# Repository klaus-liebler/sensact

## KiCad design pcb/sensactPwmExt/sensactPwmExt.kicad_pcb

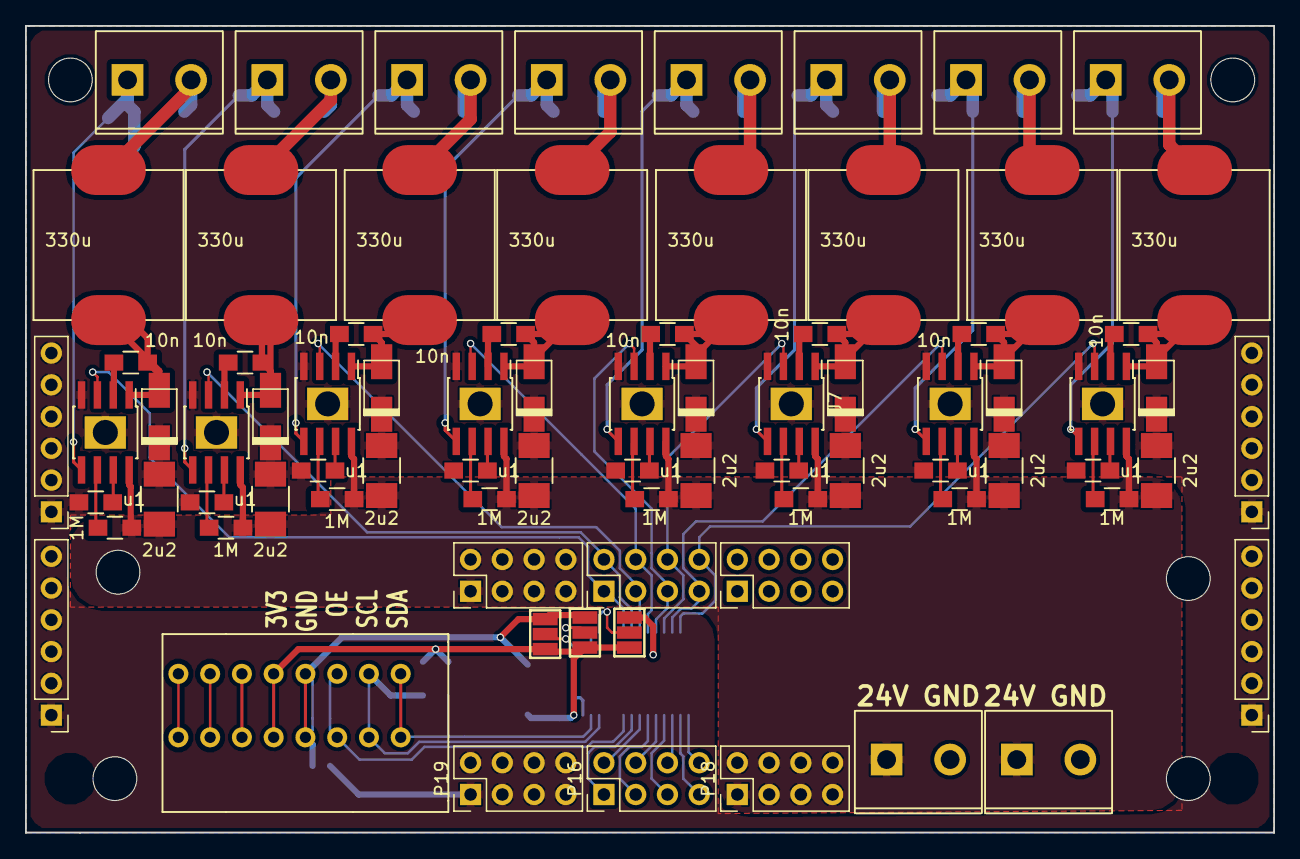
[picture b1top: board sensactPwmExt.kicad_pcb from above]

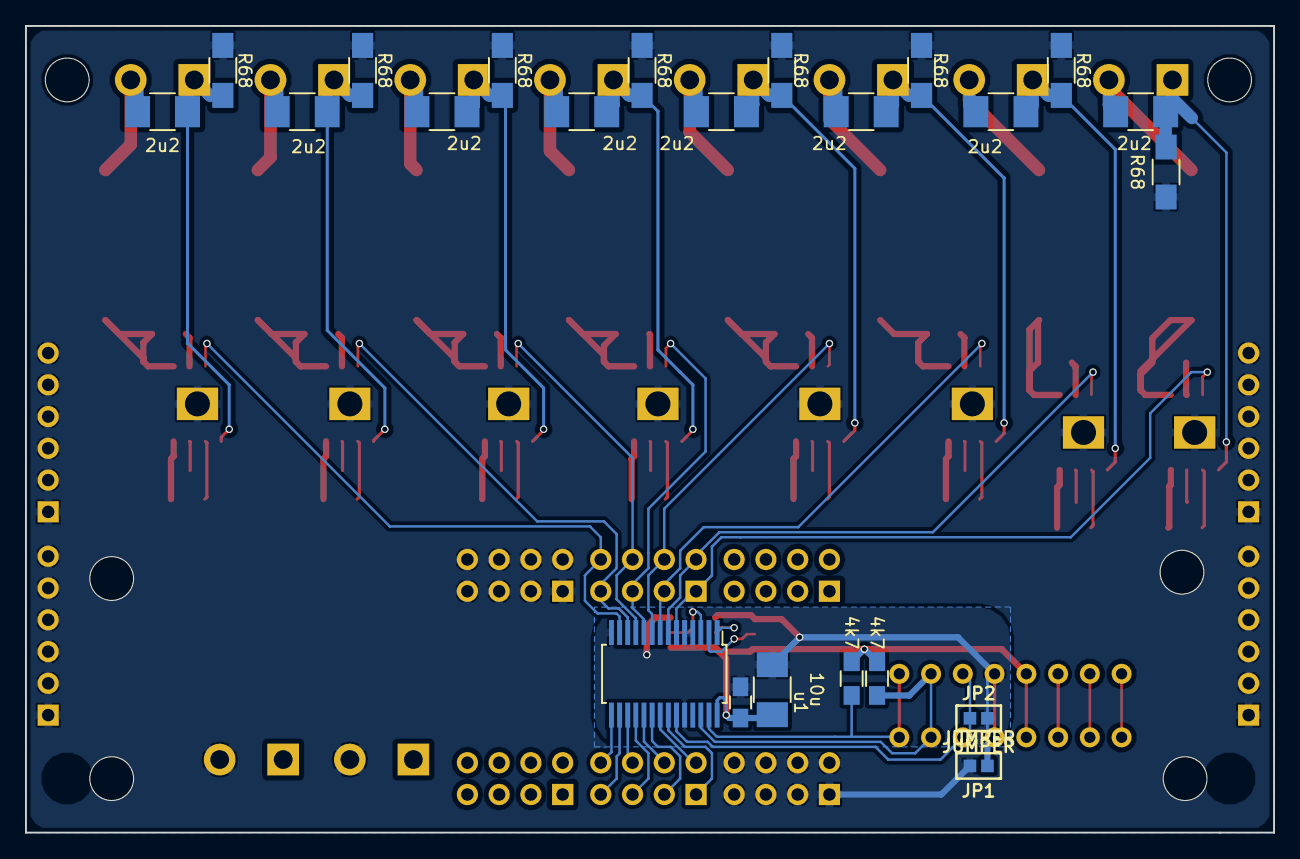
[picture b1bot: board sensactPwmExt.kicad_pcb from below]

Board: 2 copper layers, 99.8 x 64.5 mm, 109 parts (23 on the bottom side), 74 nets.

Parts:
C8: u1; C_0805_HandSoldering
C9: 10u; C_1210_HandSoldering
C10, C13, C14, C17, C18, C21, C22, C25, C26, C29, C30, C33, C34, C37, C38, C41: 2u2; R_1210_HandSoldering
C11, C15, C19, C23, C27, C31, C35, C39: 10n; R_0805_HandSoldering
C12, C16, C20, C24, C28, C32, C36, C40: u1; R_0805_HandSoldering
D1, D2, D3, D4, D5, D6, D7, D8: D_Schottky; do214ac_handsolder
JP1, JP2: JUMPER; SMD-solder-bridge
JP3, JP4, JP5: JUMPER3; SMD-solder-bridge-3pin
L1, L2, L3, L4, L5, L6, L7, L8: 330u; CD127
P1: CONN_01X08; KF141R-8p
P2, P2#2, P7, P8, P9, P10, P11, P12, P13, P14: CONN_01X02; conn_2P
P3, P4, P4#2, P5, P6, P6#2: CONN_01X01; MountingHole_3.5mm
P15, P16, P17, P18, P19, P20: CONN_01X08; Pin_Header_Straight_2x04_Pitch2.54mm
P21, P22, P23, P24: CONN_01X06; Pin_Header_Straight_1x06_Pitch2.54mm
R1, R2: 4k7; R_0805_HandSoldering
R3, R5, R7, R9, R11, R13, R15, R17: 1M; R_0805_HandSoldering
R4, R6, R8, R10, R12, R14, R16, R18: R68; R_1206_HandSoldering
U1: PCA9685; TSSOP-28_4.4x9.7mm_Pitch0.65mm_handsolder
U2, U3, U4, U5, U6, U7, U8, U9: LM3404; SOIC-8_3.9x4.9mm_Pitch1.27mm_pad_handsolder

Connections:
+3V3: C8.1, C9.1, JP3.1, JP4.1, JP5.1, P1.4, R1.1, R2.1, U1.28
+24V: C10.1, C14.1, C18.1, C22.1, C26.1, C30.1, C34.1, C38.1, P2.1, P2#2.1, P17.1, P17.2, P17.3, P17.4, P17.5, P17.6, P17.7, P17.8, P18.1, P18.2, P18.3, P18.4, P18.5, P18.6, P18.7, P18.8, R3.1, R5.1, R7.1, R9.1, R11.1, R13.1, R15.1, R17.1, U2.8, U3.8, U4.8, U5.8, U6.8, U7.8, U8.8, U9.8
/OE: JP2.1, P1.6, U1.23
/SCL: P1.7, R2.2, U1.26
/SDA: P1.8, R1.2, U1.27
/pwm1/LED+: C13.1, L1.1, P7.2
/pwm1/LED-: C13.2, P7.1, R4.1, U2.5
/pwm1/PWM_IN: P15.1, U1.6, U2.3
/pwm2/LED+: C17.1, L2.1, P8.2
/pwm2/LED-: C17.2, P8.1, R6.1, U3.5
/pwm2/PWM_IN: P15.2, U1.7, U3.3
/pwm3/LED+: C21.1, L3.1, P9.2
/pwm3/LED-: C21.2, P9.1, R8.1, U4.5
/pwm3/PWM_IN: P15.3, U1.8, U4.3
/pwm4/LED+: C25.1, L4.1, P10.2
/pwm4/LED-: C25.2, P10.1, R10.1, U5.5
/pwm4/PWM_IN: P15.4, U1.9, U5.3
/pwm5/LED+: C29.1, L5.1, P11.2
/pwm5/LED-: C29.2, P11.1, R12.1, U6.5
/pwm5/PWM_IN: P15.5, U1.10, U6.3
/pwm6/LED+: C33.1, L6.1, P12.2
/pwm6/LED-: C33.2, P12.1, R14.1, U7.5
/pwm6/PWM_IN: P15.6, U1.11, U7.3
/pwm7/LED+: C37.1, L7.1, P13.2
/pwm7/LED-: C37.2, P13.1, R16.1, U8.5
/pwm7/PWM_IN: P15.7, U1.12, U8.3
/pwm8/LED+: C41.1, L8.1, P14.2
/pwm8/LED-: C41.2, P14.1, R18.1, U9.5
/pwm8/PWM_IN: P15.8, U1.13, U9.3
GND: C10.2, C12.2, C14.2, C16.2, C18.2, C20.2, C22.2, C24.2, C26.2, C28.2, C30.2, C32.2, C34.2, C36.2, C38.2, C40.2, D1.2, D2.2, D3.2, D4.2, D5.2, D6.2, D7.2, D8.2, JP1.2, P2.2, P2#2.2, P19.1, P19.2, P19.3, P19.4, P19.5, P19.6, P19.7, P19.8, P20.1, P20.2, P20.3, P20.4, P20.5, P20.6, P20.7, P20.8, P21.1, P21.2, P21.3, P21.4, P21.5, P21.6, P22.1, P22.2, P22.3, P22.4, P22.5, P22.6, P23.1, P23.2, P23.3, P23.4, P23.5, P23.6, P24.1, P24.2, P24.3, P24.4, P24.5, P24.6, R4.2, R6.2, R8.2, R10.2, R12.2, R14.2, R16.2, R18.2, U2.4, U2.9, U3.4, U3.9, U4.4, U4.9, U5.4, U5.9, U6.4, U6.9, U7.4, U7.9, U8.4, U8.9, U9.4, U9.9
GNDA: C8.2, C9.2, JP1.1, JP2.2, JP3.3, JP4.3, JP5.3, P1.5, U1.4, U1.5, U1.14, U1.24
unnamed: C11.1, D1.1, L1.2, U2.1
unnamed: C11.2, U2.2
unnamed: C12.1, U2.7
unnamed: C15.1, D2.1, L2.2, U3.1
unnamed: C15.2, U3.2
unnamed: C16.1, U3.7
unnamed: C19.1, D3.1, L3.2, U4.1
unnamed: C19.2, U4.2
unnamed: C20.1, U4.7
unnamed: C23.1, D4.1, L4.2, U5.1
unnamed: C23.2, U5.2
unnamed: C24.1, U5.7
unnamed: C27.1, D5.1, L5.2, U6.1
unnamed: C27.2, U6.2
unnamed: C28.1, U6.7
unnamed: C31.1, D6.1, L6.2, U7.1
unnamed: C31.2, U7.2
unnamed: C32.1, U7.7
unnamed: C35.1, D7.1, L7.2, U8.1
unnamed: C35.2, U8.2
unnamed: C36.1, U8.7
unnamed: C39.1, D8.1, L8.2, U9.1
unnamed: C39.2, U9.2
unnamed: C40.1, U9.7
unnamed: JP3.2, U1.1
unnamed: JP4.2, U1.2
unnamed: JP5.2, U1.3
unnamed: P16.1, U1.22
unnamed: P16.2, U1.21
unnamed: P16.3, U1.20
unnamed: P16.4, U1.19
unnamed: P16.5, U1.18
unnamed: P16.6, U1.17
unnamed: P16.7, U1.16
unnamed: P16.8, U1.15
unnamed: R3.2, U2.6
unnamed: R5.2, U3.6
unnamed: R7.2, U4.6
unnamed: R9.2, U5.6
unnamed: R11.2, U6.6
unnamed: R13.2, U7.6
unnamed: R15.2, U8.6
unnamed: R17.2, U9.6

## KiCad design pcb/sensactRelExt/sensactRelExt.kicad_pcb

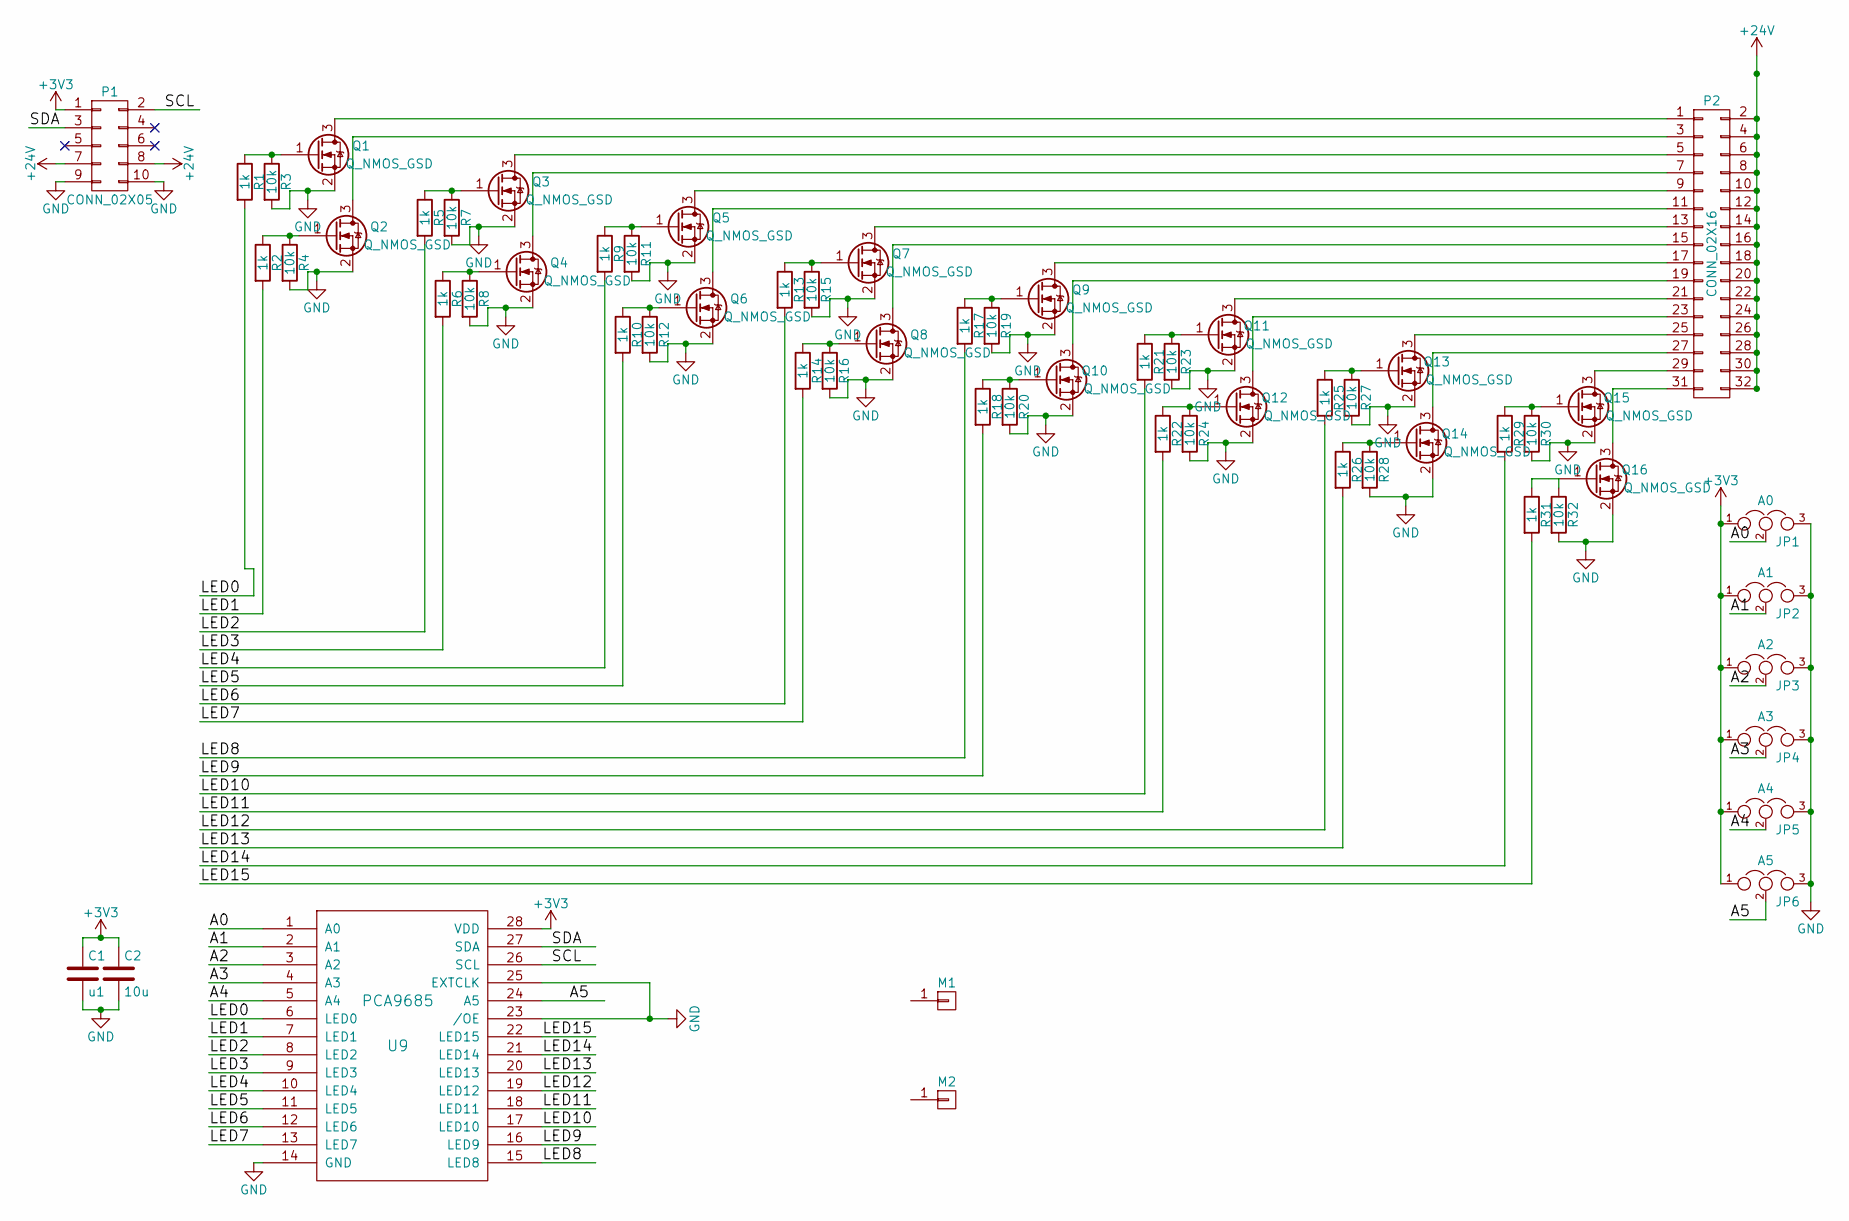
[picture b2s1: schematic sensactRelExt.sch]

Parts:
C1: u1; C_0805_HandSoldering
C2: 10u; C_1206_HandSoldering
JP1: A0; SMD-solder-bridge-3pin
JP2: A1; SMD-solder-bridge-3pin
JP3: A2; SMD-solder-bridge-3pin
JP4: A3; SMD-solder-bridge-3pin
JP5: A4; SMD-solder-bridge-3pin
JP6: A5; SMD-solder-bridge-3pin
M1, M2: CONN_01X01; MountingHole_4.3mm_M4_DIN965
P1: CONN_02X05; vasch_strip_5x2
P2: CONN_02X16; vasch_strip_16x2
Q1, Q2, Q3, Q4, Q5, Q6, Q7, Q8, Q9, Q10, Q11, Q12, Q13, Q14, Q15, Q16: Q_NMOS_GSD; SOT-23_Handsoldering
R1, R2, R5, R6, R9, R10, R13, R14, R17, R18, R21, R22, R25, R26, R29, R31: 1k; R_0805_HandSoldering
R3, R4, R7, R8, R11, R12, R15, R16, R19, R20, R23, R24, R27, R28, R30, R32: 10k; R_0805_HandSoldering
U9: PCA9685; TSSOP-28_4.4x9.7mm_Pitch0.65mm_handsolder

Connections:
+3V3: C1.1, C2.1, JP1.1, JP2.1, JP3.1, JP4.1, JP5.1, JP6.1, P1.1, U9.28 (VDD)
+24V: P1.7, P1.8, P2.2, P2.4, P2.6, P2.8, P2.10, P2.12, P2.14, P2.16, P2.18, P2.20, P2.22, P2.24, P2.26, P2.28, P2.30, P2.32
/A0: JP1.2, U9.1 (A0)
/A1: JP2.2, U9.2 (A1)
/A2: JP3.2, U9.3 (A2)
/A3: JP4.2, U9.4 (A3)
/A4: JP5.2, U9.5 (A4)
/A5: JP6.2, U9.24 (A5)
/LED0: R1.2, U9.6 (LED0)
/LED1: R2.2, U9.7 (LED1)
/LED2: R5.2, U9.8 (LED2)
/LED3: R6.2, U9.9 (LED3)
/LED4: R9.2, U9.10 (LED4)
/LED5: R10.2, U9.11 (LED5)
/LED6: R13.2, U9.12 (LED6)
/LED7: R14.2, U9.13 (LED7)
/LED8: R17.2, U9.15 (LED8)
/LED9: R18.2, U9.16 (LED9)
/LED10: R21.2, U9.17 (LED10)
/LED11: R22.2, U9.18 (LED11)
/LED12: R25.2, U9.19 (LED12)
/LED13: R26.2, U9.20 (LED13)
/LED14: R29.2, U9.21 (LED14)
/LED15: R31.2, U9.22 (LED15)
/SCL: P1.2, U9.26 (SCL)
/SDA: P1.3, U9.27 (SDA)
GND: C1.2, C2.2, JP1.3, JP2.3, JP3.3, JP4.3, JP5.3, JP6.3, P1.9, P1.10, Q1.2 (S), Q2.2 (S), Q3.2 (S), Q4.2 (S), Q5.2 (S), Q6.2 (S), Q7.2 (S), Q8.2 (S), Q9.2 (S), Q10.2 (S), Q11.2 (S), Q12.2 (S), Q13.2 (S), Q14.2 (S), Q15.2 (S), Q16.2 (S), R3.2, R4.2, R7.2, R8.2, R11.2, R12.2, R15.2, R16.2, R19.2, R20.2, R23.2, R24.2, R27.2, R28.2, R30.2, R32.2, U9.14 (GND), U9.23 (/OE), U9.25 (EXTCLK)
unnamed: P2.1, Q1.3 (D)
unnamed: P2.3, Q2.3 (D)
unnamed: P2.5, Q3.3 (D)
unnamed: P2.7, Q4.3 (D)
unnamed: P2.9, Q5.3 (D)
unnamed: P2.11, Q6.3 (D)
unnamed: P2.13, Q7.3 (D)
unnamed: P2.15, Q8.3 (D)
unnamed: P2.17, Q9.3 (D)
unnamed: P2.19, Q10.3 (D)
unnamed: P2.21, Q11.3 (D)
unnamed: P2.23, Q12.3 (D)
unnamed: P2.25, Q13.3 (D)
unnamed: P2.27, Q14.3 (D)
unnamed: P2.29, Q15.3 (D)
unnamed: P2.31, Q16.3 (D)
unnamed: Q1.1 (G), R1.1, R3.1
unnamed: Q2.1 (G), R2.1, R4.1
unnamed: Q3.1 (G), R5.1, R7.1
unnamed: Q4.1 (G), R6.1, R8.1
unnamed: Q5.1 (G), R9.1, R11.1
unnamed: Q6.1 (G), R10.1, R12.1
unnamed: Q7.1 (G), R13.1, R15.1
unnamed: Q8.1 (G), R14.1, R16.1
unnamed: Q9.1 (G), R17.1, R19.1
unnamed: Q10.1 (G), R18.1, R20.1
unnamed: Q11.1 (G), R21.1, R23.1
unnamed: Q12.1 (G), R22.1, R24.1
unnamed: Q13.1 (G), R25.1, R27.1
unnamed: Q14.1 (G), R26.1, R28.1
unnamed: Q15.1 (G), R29.1, R30.1
unnamed: Q16.1 (G), R31.1, R32.1

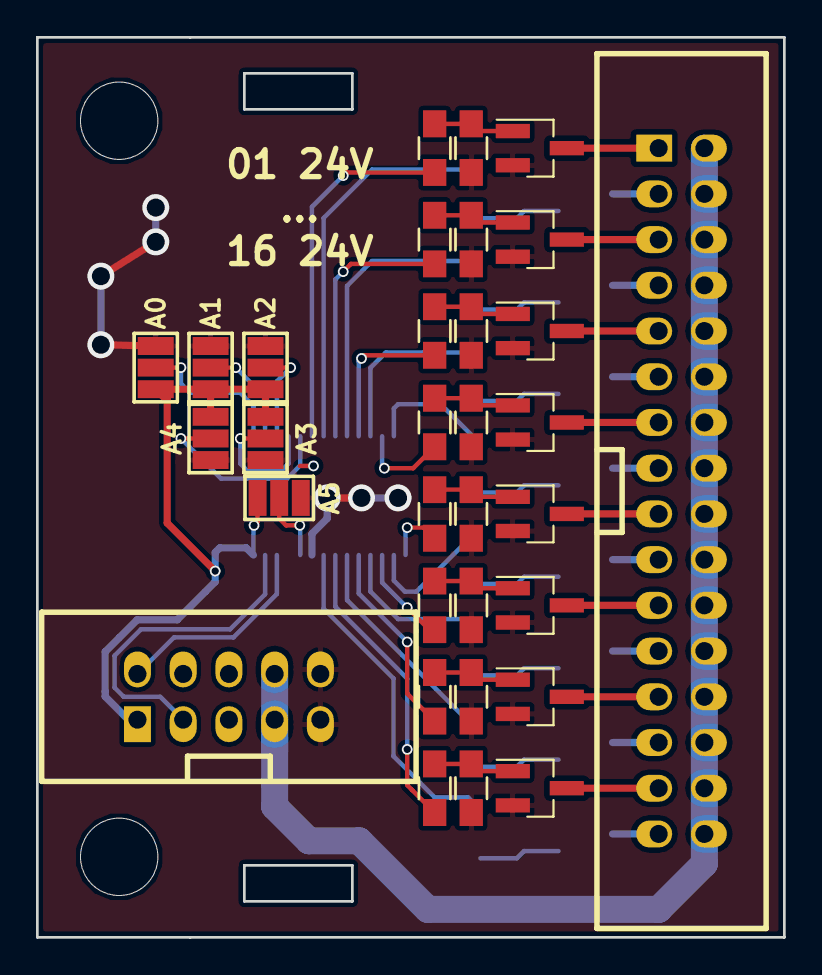
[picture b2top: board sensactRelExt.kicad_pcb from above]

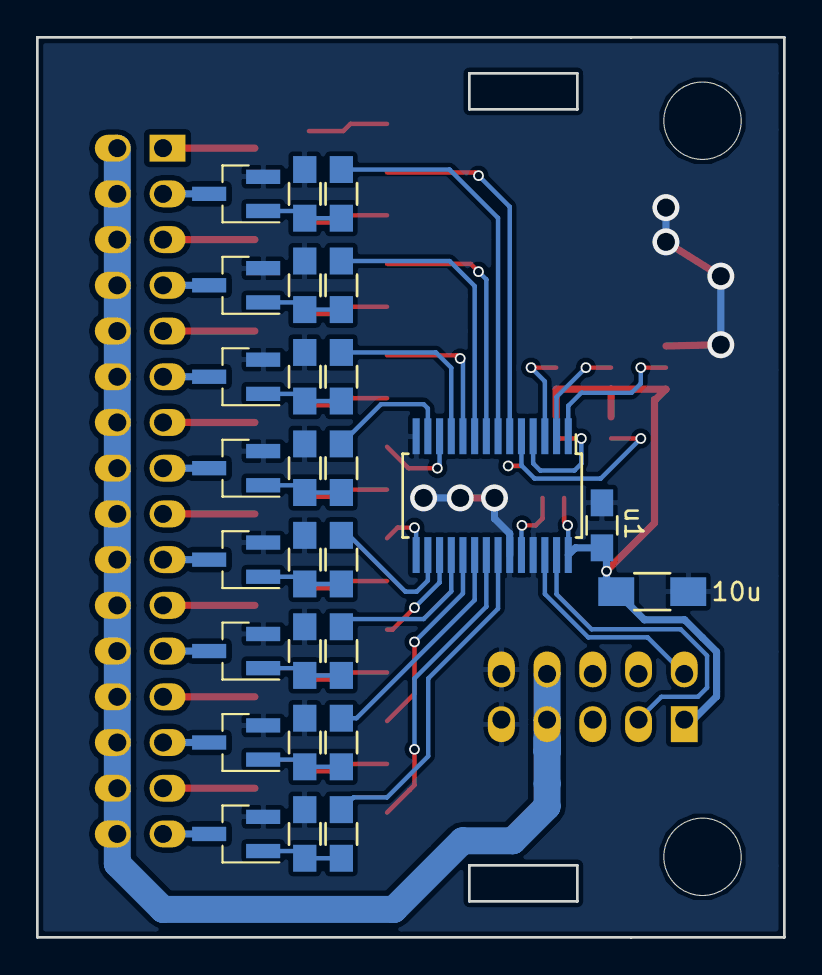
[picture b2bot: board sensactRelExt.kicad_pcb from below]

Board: 2 copper layers, 41.5 x 50.0 mm, 61 parts (27 on the bottom side), 59 nets.

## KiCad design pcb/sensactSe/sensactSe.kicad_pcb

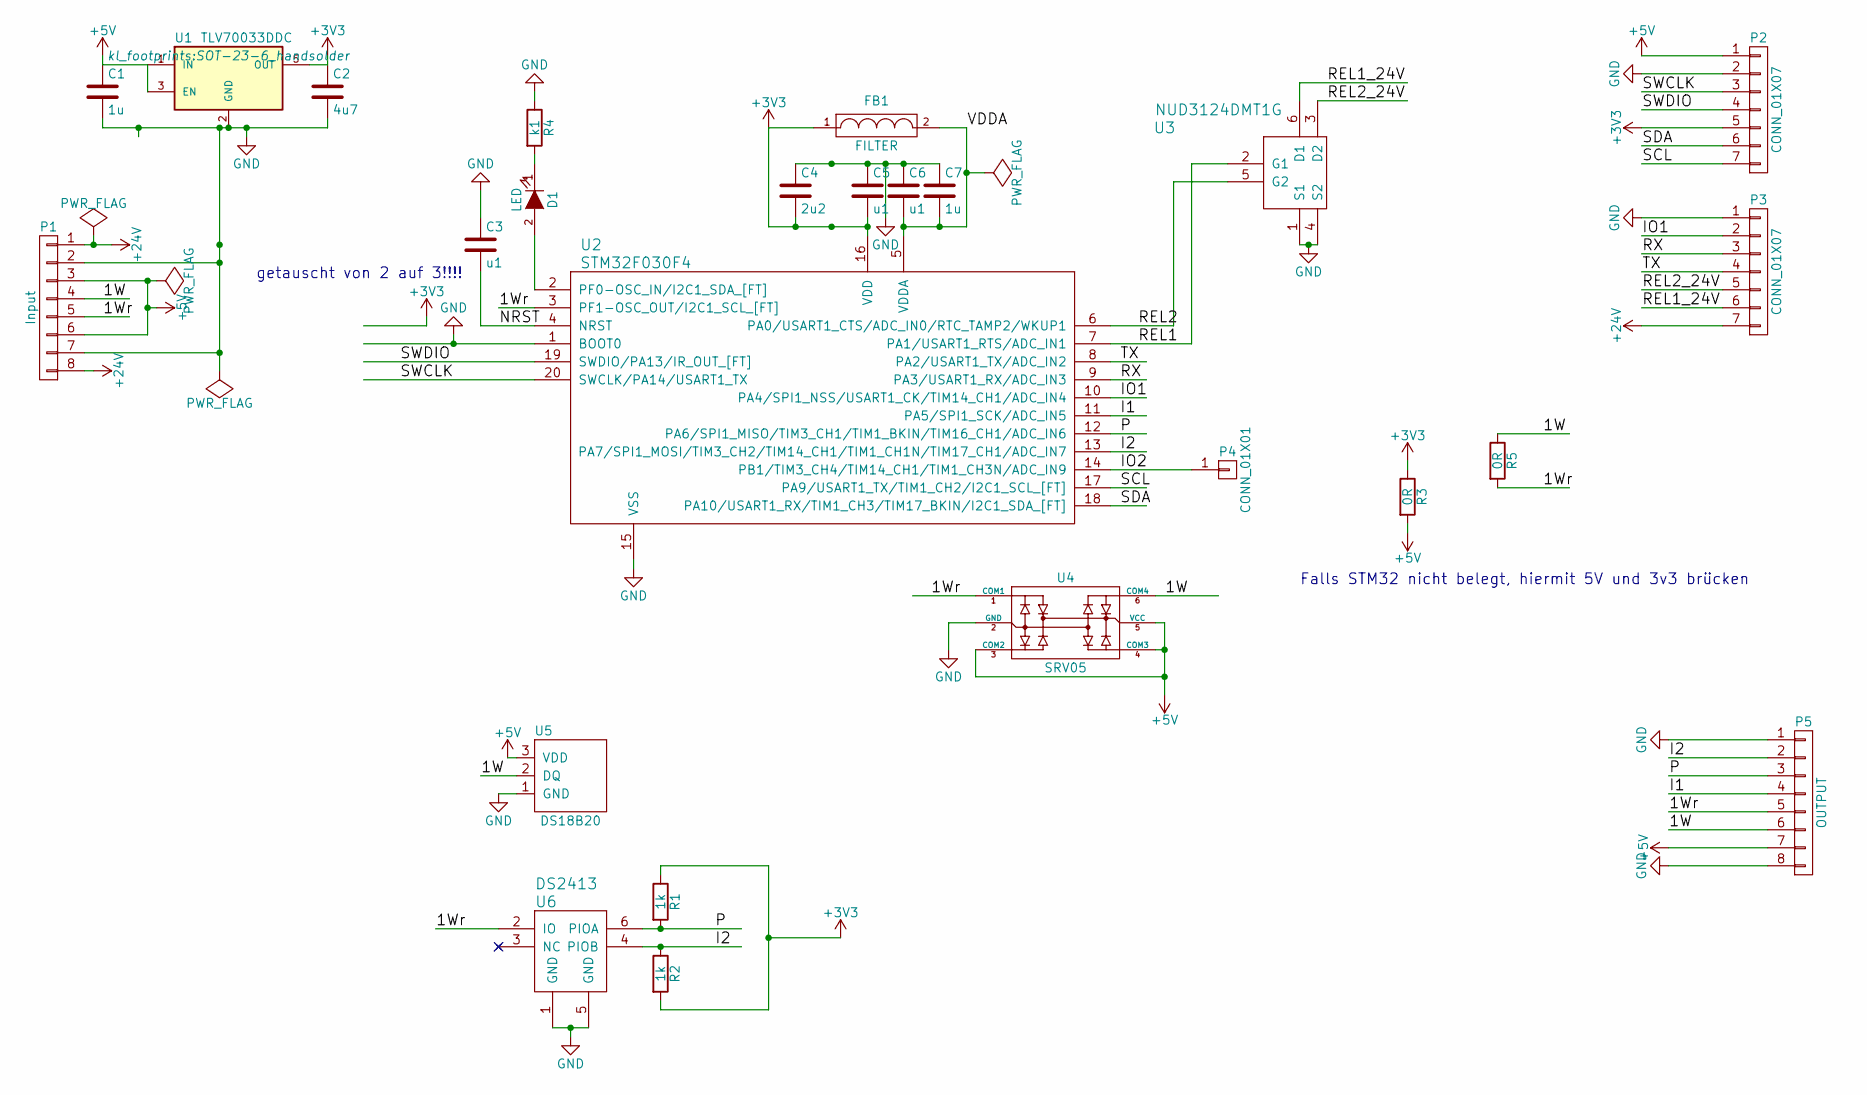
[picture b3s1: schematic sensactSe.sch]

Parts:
C1, C7: 1u; C_0805_HandSoldering
C2: 4u7; C_1206_HandSoldering
C3, C5, C6: u1; C_0805_HandSoldering
C4: 2u2; C_0805_HandSoldering
D1: LED; R_0805_HandSoldering
FB1: FILTER; C_1206_HandSoldering
P1: Input; KF141R-8p
P2, P3: CONN_01X07; Pin_Header_Straight_1x07
P4: CONN_01X01; Measurement_Point_Square-TH_Small
P5: OUTPUT; KF141R-8p
R1, R2: 1k; R_0805_HandSoldering
R3, R5: 0R; R_0805_HandSoldering
R4: k1; R_0805_HandSoldering
U1: TLV70033DDC; SOT-23-6_handsolder
U2: STM32F030F4; TSSOP-20_4.4x6.5mm_Pitch0.65mm_handsolder
U3: NUD3124DMT1G; SOT-23-6_handsolder
U4: SRV05; SOT-23-6_handsolder
U5: DS18B20; TO-92_Inline_Narrow_Oval
U6: DS2413; TSOC6

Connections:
+3V3: C2.1, C4.2, C5.2, FB1.1, P2.5, R1.1, R2.2, R3.1, U1.5 (OUT), U2.16 (VDD)
+5V: C1.1, P1.3, P1.6, P2.1, P5.7, R3.2, U1.1 (IN), U1.3 (EN), U4.3 (COM2), U4.4 (COM3), U4.5 (VCC), U5.3 (VDD)
+24V: P1.1, P1.8, P3.7
/1W: P1.4, P5.6, R5.1, U4.6 (COM4), U5.2 (DQ)
/1Wr: P1.5, P5.5, R5.2, U2.3 (PF1-OSC_OUT/I2C1_SCL_[FT]), U4.1 (COM1), U6.2 (IO)
/I1: P5.4, U2.11 (PA5/SPI1_SCK/ADC_IN5)
/I2: P5.2, R2.1, U2.13 (PA7/SPI1_MOSI/TIM3_CH2/TIM14_CH1/TIM1_C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), U6.4 (PIOB)
/IO1: P3.2, U2.10 (PA4/SPI1_NSS/USART1_CK/TIM14_CH1/ADC_IN4)
/IO2: P4.1, U2.14 (PB1/TIM3_CH4/TIM14_CH1/TIM1_CH3N/ADC_IN9)
/NRST: C3.2, U2.4 (NRST)
/P: P5.3, R1.2, U2.12 (PA6/SPI1_MISO/TIM3_CH1/TIM1_BKIN/TIM16_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), U6.6 (PIOA)
/REL1: U2.7 (PA1/USART1_RTS/ADC_IN1), U3.2 (G1)
/REL1_24V: P3.6, U3.6 (D1)
/REL2: U2.6 (PA0/USART1_CTS/ADC_IN0/RTC_TAMP2/WKUP1), U3.5 (G2)
/REL2_24V: P3.5, U3.3 (D2)
/RX: P3.3, U2.9 (PA3/USART1_RX/ADC_IN3)
/SCL: P2.7, U2.17 (PA9/USART1_TX/TIM1_CH2/I2C1_SCL_[FT])
/SDA: P2.6, U2.18 (PA10/USART1_RX/TIM1_CH3/TIM17_BKIN/I2C1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)
/SWCLK: P2.3, U2.20 (SWCLK/PA14/USART1_TX)
/SWDIO: P2.4, U2.19 (SWDIO/PA13/IR_OUT_[FT])
/TX: P3.4, U2.8 (PA2/USART1_TX/ADC_IN2)
/VDDA: C6.2, C7.2, FB1.2, U2.5 (VDDA)
GND: C1.2, C2.2, C3.1, C4.1, C5.1, C6.1, C7.1, P1.2, P1.7, P2.2, P3.1, P5.1, P5.8, R4.1, U1.2 (GND), U2.1 (BOOT0), U2.15 (VSS), U3.1 (S1), U3.4 (S2), U4.2 (GND), U5.1 (GND), U6.1 (GND), U6.5 (GND)
unnamed: D1.1 (K), R4.2
unnamed: D1.2 (A), U2.2 (PF0-OSC_IN/I2C1_SDA_[FT])

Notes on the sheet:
Falls STM32 nicht belegt, hiermit 5V und 3v3 brücken
getauscht von 2 auf 3!!!!

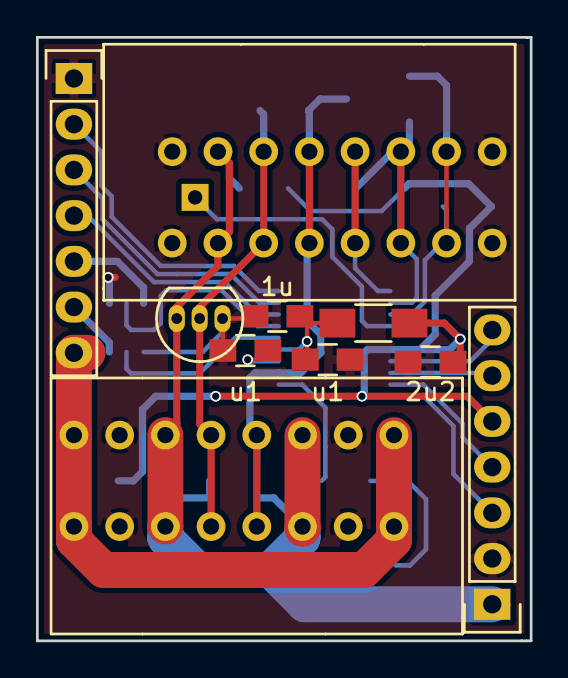
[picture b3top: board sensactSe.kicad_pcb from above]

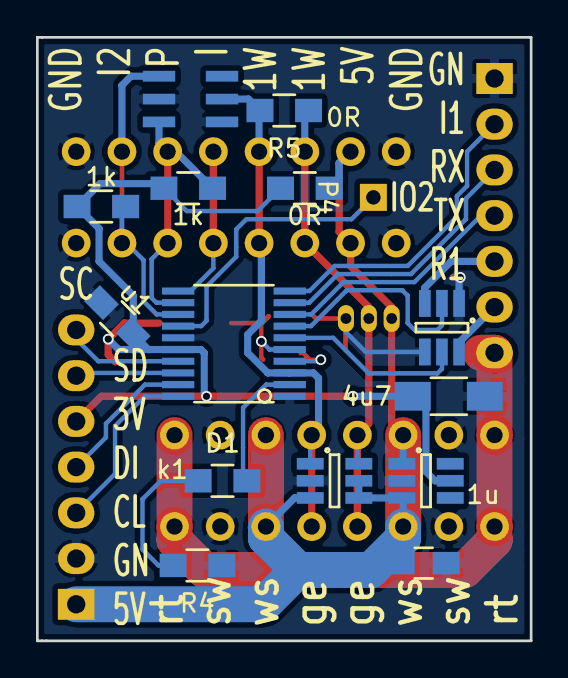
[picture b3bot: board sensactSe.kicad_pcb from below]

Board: 2 copper layers, 27.4 x 33.5 mm, 25 parts (15 on the bottom side), 25 nets.

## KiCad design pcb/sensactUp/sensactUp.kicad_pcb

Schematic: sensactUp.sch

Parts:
C1, C6: m1; C_1206_HandSoldering
C2, C5: 4u7; C_1206_HandSoldering
C3, C4, C9, C10, C11, C12, C13, C14, C21, C23, C25: u1; C_0805_HandSoldering
C22: u1_1u; C_0805_HandSoldering
C24: 22p; C_0805_HandSoldering
D1, D3: MBR0540; do214ac_handsolder
D2: MBR0540; sod123_handsolder
D4, D5, D6, D7, D8: WS2812B; PLCC4-5050
L1: 150u; PowerInductor_7mm
L2: 100u; PowerInductor_7mm
MK1, MK2, MK3, MK4, MK5: Mounting_Hole; MountingHole_3.2mm_M3
O1: IO; vasch_strip_8x2
P1: CONN_01X06; MicroUsbVertical
P2: PWR; KF141R-2p_1234
P3: CAN; KF141R-2p_1234
P4, P6, P10, P14: CONN_02X05; Pin_Header_Straight_2x05_Pitch2.54mm
P5, P8: CONN_02X02; Pin_Header_Straight_2x02_Pitch2.54mm
P9: CCS811; Pin_Header_Straight_1x08_Pitch2.54mm
P11: SENSACT BUS; vasch_strip_5x2
P12: 6/8; Pin_Header_Straight_1x02_Pitch2.54mm
P13: 5/L; Pin_Header_Straight_1x02_Pitch2.54mm
P15, P16, P17: CONN_02X07; Pin_Header_Straight_2x07_Pitch2.54mm
P18: SI7021; Pin_Header_Straight_1x04_Pitch2.54mm
Q1, Q2, Q3, Q4: Q_NMOS_GSD; SOT-23_Handsoldering
R1, R5, R6, R10, R11, R13, R15, R17, R19, R21: 1k; R_0805_HandSoldering
R2: 22k; R_0805_HandSoldering
R3, R8, R14: 4k7; R_0805_HandSoldering
R4: 3k3; R_0805_HandSoldering
R12, R16, R18, R20, R22, R24: 10k; R_0805_HandSoldering
R23: 6k8; R_1206_HandSoldering
SW1: ROTARY_ENCODER_SWITCH_CASE; encoder_alps-ec12d_case
SW2: RESET; SW_PUSH_6mm
U1, U2: LMR14006; SOT-23-6_handsolder
U4: TLV70033DDC; SOT-23-5_handsolder
U5: TJA1021T; SOIC-8_3.9x4.9mm_Pitch1.27mm_handsolder
U6: M25PX32-VMW; SOIJ-8_5.3x5.3mm_Pitch1.27mm_handsolder
U9: SN65HVD230; SOIC-8_3.9x4.9mm_Pitch1.27mm_handsolder

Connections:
+3V3: C1.1, C22.2, C23.1, L1.2, O1.5, P4.3, P4.4, P8.1, P8.2, P9.1, P10.2, P10.4, P10.6, P10.8, P10.9, P10.10, P11.1, P17.13, P17.14, P18.4, R1.1, R4.1, R5.1, R8.1, R13.1, R14.1, R15.1, R24.1, U4.5 (OUT), U6.8 (VCC), U9.3 (VCC); also elsewhere on the board
+5V: C6.1, C10.1, C11.1, C12.1, C13.1, C14.1, D4.1 (VDD), D5.1 (VDD), D6.1 (VDD), D7.1 (VDD), D8.1 (VDD), L2.2, P4.1, P4.2, P6.1, P6.3, P14.7, P14.8, P14.9, P14.10, P15.13, P15.14, P17.11, P17.12, R2.1
+24V: C2.1, C5.1, C25.1, D3.1 (K), U1.5 (VIN), U2.5 (VIN), U5.3 (~WAKE~), U5.7 (VBAT)
/24VX: D3.2 (A), P2.1, P2.2, P5.3, P5.4, P11.7, P11.8, P14.3, P14.4, P14.5, P14.6, P16.2, P16.4, P16.6, P16.8, P16.10, P16.12, P16.14
/24Vin: O1.8, R23.1
/CANH_LIN: C24.1, P3.4, U5.6 (LIN), U9.7 (CANH)
/CANL_5V: C21.1, P3.2, U4.1 (IN), U4.3 (EN), U9.6 (CANL)
/O24_1: P12.2, Q1.3 (D)
/O24_2: P12.1, Q2.3 (D)
/O24_3: P13.1, Q3.3 (D)
/O24_4: P13.2, Q4.3 (D)
/SW3V: C3.1, D2.1 (K), L1.1, U2.6 (SW)
/SW5V: C4.1, D1.1 (K), L2.1, U1.6 (SW)
/WS2812OUT: D6.2 (DOUT), O1.7
CANR: U9.4 (R/RXD)
CANT: U9.1 (D/TXD)
GND: C1.2, C2.2, C5.2, C6.2, C9.1, C10.2, C11.2, C12.2, C13.2, C14.2, C21.2, C22.1, C23.2, C24.2, C25.2, D1.2 (A), D2.2 (A), D4.3 (VSS), D5.3 (VSS), D6.3 (VSS), D7.3 (VSS), D8.3 (VSS), O1.16, P1.2, P1.6, P2.3, P2.4, P4.5, P4.6, P4.7, P4.8, P4.9, P4.10, P5.1, P5.2, P6.2, P6.4, P8.3, P8.4, P9.2, P9.5, P9.8, P10.1, P10.3, P11.9, P11.10, P14.1, P14.2, P18.3, Q1.2 (S), Q2.2 (S), Q3.2 (S), Q4.2 (S), R3.2, R6.2, R10.2, R12.1, R16.2, R18.2, R20.2, R22.2, SW1.2 (C), SW1.5, SW1.6 (CASE), SW2.1, U1.2 (GND), U2.2 (GND), U4.2 (GND), U5.5 (GND), U6.4 (VSS), U9.2 (GND); also elsewhere on the board
INT1: P11.4
INT2: P9.7, P11.5
INT3: P9.6, P11.6
IO1: R10.1, R23.2
IO2: O1.9
IO3: O1.10, U6.1 (S#)
IO4: O1.11, U6.6 (C)
IO5: O1.12, R19.1, U6.2 (DQ1)
IO6: O1.13, R17.1, U6.5 (DQ0)
IO7: O1.14
IO8: O1.15, R11.1
LINRX: R24.2, U5.4 (RXD)
LINTX: R21.1, U5.1 (TXD)
NRST: C9.2, SW2.2
unnamed: C3.2, U2.1 (CB)
unnamed: C4.2, U1.1 (CB)
unnamed: D4.2 (DOUT), D7.4 (DIN)
unnamed: D5.2 (DOUT), D6.4 (DIN)
unnamed: D5.4 (DIN), D8.2 (DOUT)
unnamed: D7.2 (DOUT), D8.4 (DIN)
unnamed: Q1.1 (G), R11.2, R16.1
unnamed: Q2.1 (G), R17.2, R18.1
unnamed: Q3.1 (G), R19.2, R20.1
unnamed: Q4.1 (G), R21.2, R22.1
unnamed: R2.2, R3.1, U1.3 (FB)
unnamed: R4.2, R6.1, U2.3 (FB)
unnamed: R12.2, U9.8 (RS)
ROTA: R15.2, SW1.1 (A)
ROTB: R13.2, SW1.3 (B)
ROTD: SW1.4
RX: P1.5
SCL: P9.3, P11.2, P18.2, R14.2
SCL1: O1.4
SDA: P9.4, P11.3, P18.1, R8.2
SDA1: O1.6
SHDN: U1.4 (~SHDN), U5.2 (~SLP~)
SWCLK: P1.1
SWDIO: P1.3
TX: P1.4
WS2812: D4.4 (DIN)
xROTA: O1.3, R5.2
xROTB: O1.2, R1.2
xROTD: O1.1

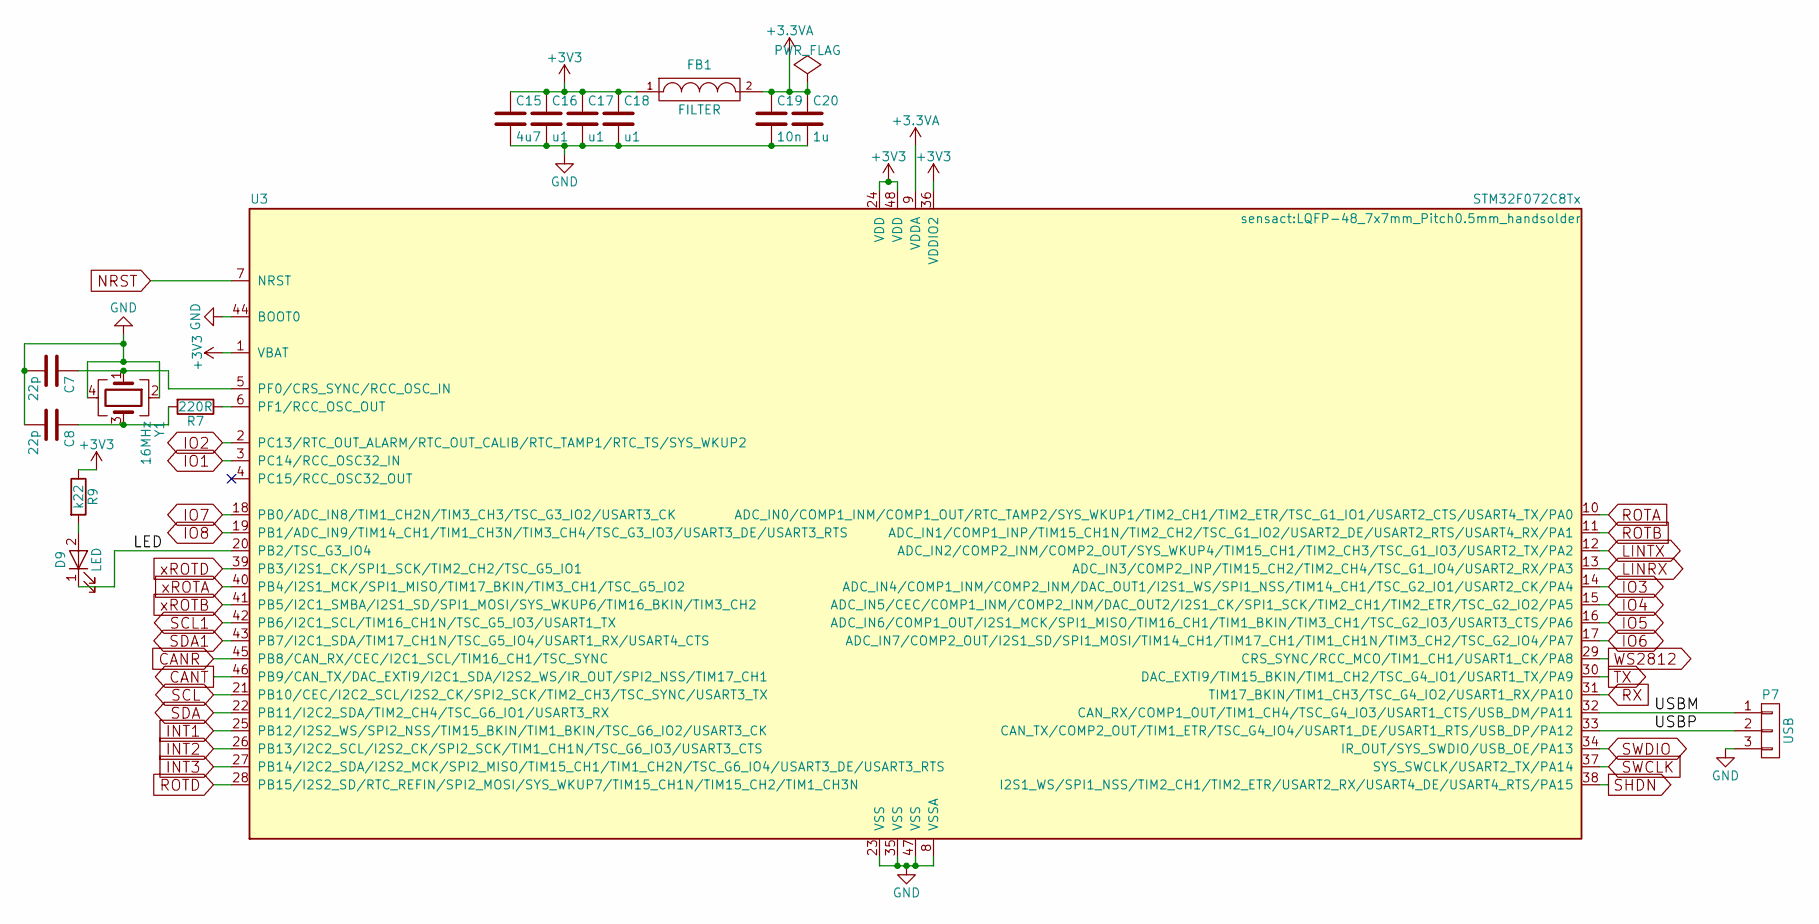
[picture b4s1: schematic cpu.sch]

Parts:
C7, C8: 22p; C_0805_HandSoldering
C15: 4u7; C_1206_HandSoldering
C16, C17, C18: u1; C_0805_HandSoldering
C19: 10n; C_0805_HandSoldering
C20: 1u; C_0805_HandSoldering
D9: LED; LED_0805_handsolder
FB1: FILTER; R_1206_HandSoldering
P7: USB; Pin_Header_Straight_1x03_Pitch2.00mm
R7: 220R; R_0805_HandSoldering
R9: k22; R_0805_HandSoldering
U3: STM32F072C8Tx; LQFP-48_7x7mm_Pitch0.5mm_handsolder
Y1: 16MHz; quartz3225

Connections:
+3.3VA: C19.1, C20.1, FB1.2, U3.9 (VDDA)
+3V3: C15.1, C16.1, C17.1, C18.1, FB1.1, R9.1, U3.1 (VBAT), U3.24 (VDD), U3.36 (VDDIO2), U3.48 (VDD); also elsewhere on the board
/cpu/LED: D9.1 (K), U3.20 (PB2/TSC_G3_IO4)
/cpu/USBM: P7.1, U3.32 (CAN_RX/COMP1_OUT/TIM1_CH4/TSC_G4_IO3/US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)
/cpu/USBP: P7.2, U3.33 (CAN_TX/COMP2_OUT/TIM1_ETR/TSC_G4_IO4/US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)
GND: C7.2, C8.2, C15.2, C16.2, C17.2, C18.2, C19.2, C20.2, P7.3, U3.8 (VSSA), U3.23 (VSS), U3.35 (VSS), U3.44 (BOOT0), U3.47 (VSS), Y1.2, Y1.4; also elsewhere on the board
unnamed: C7.1, U3.5 (PF0/CRS_SYNC/RCC_OSC_IN), Y1.1
unnamed: C8.1, R7.2, Y1.3
unnamed: D9.2 (A), R9.2
unnamed: R7.1, U3.6 (PF1/RCC_OSC_OUT)

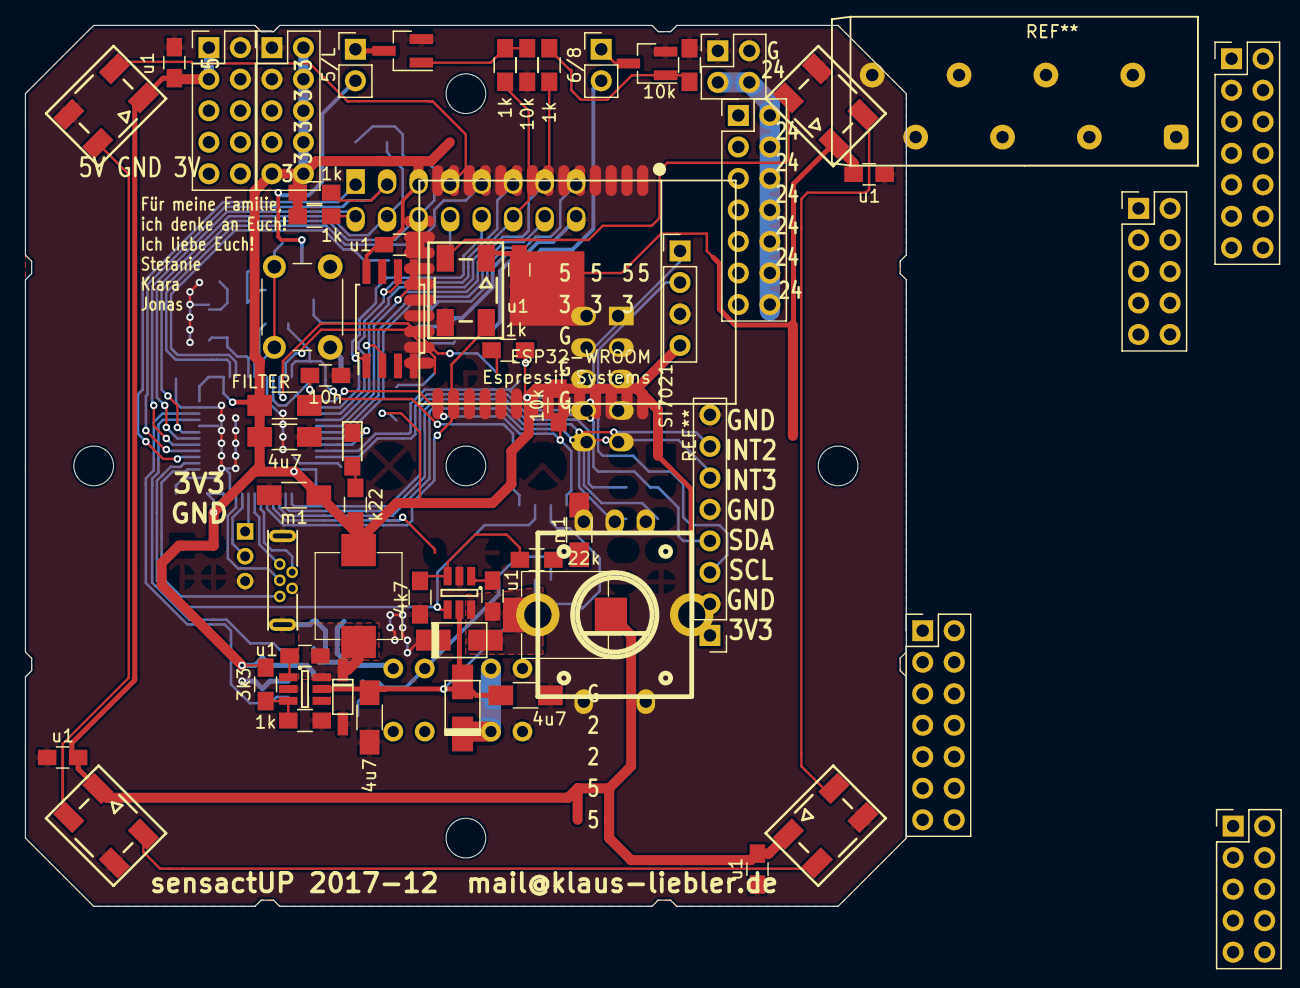
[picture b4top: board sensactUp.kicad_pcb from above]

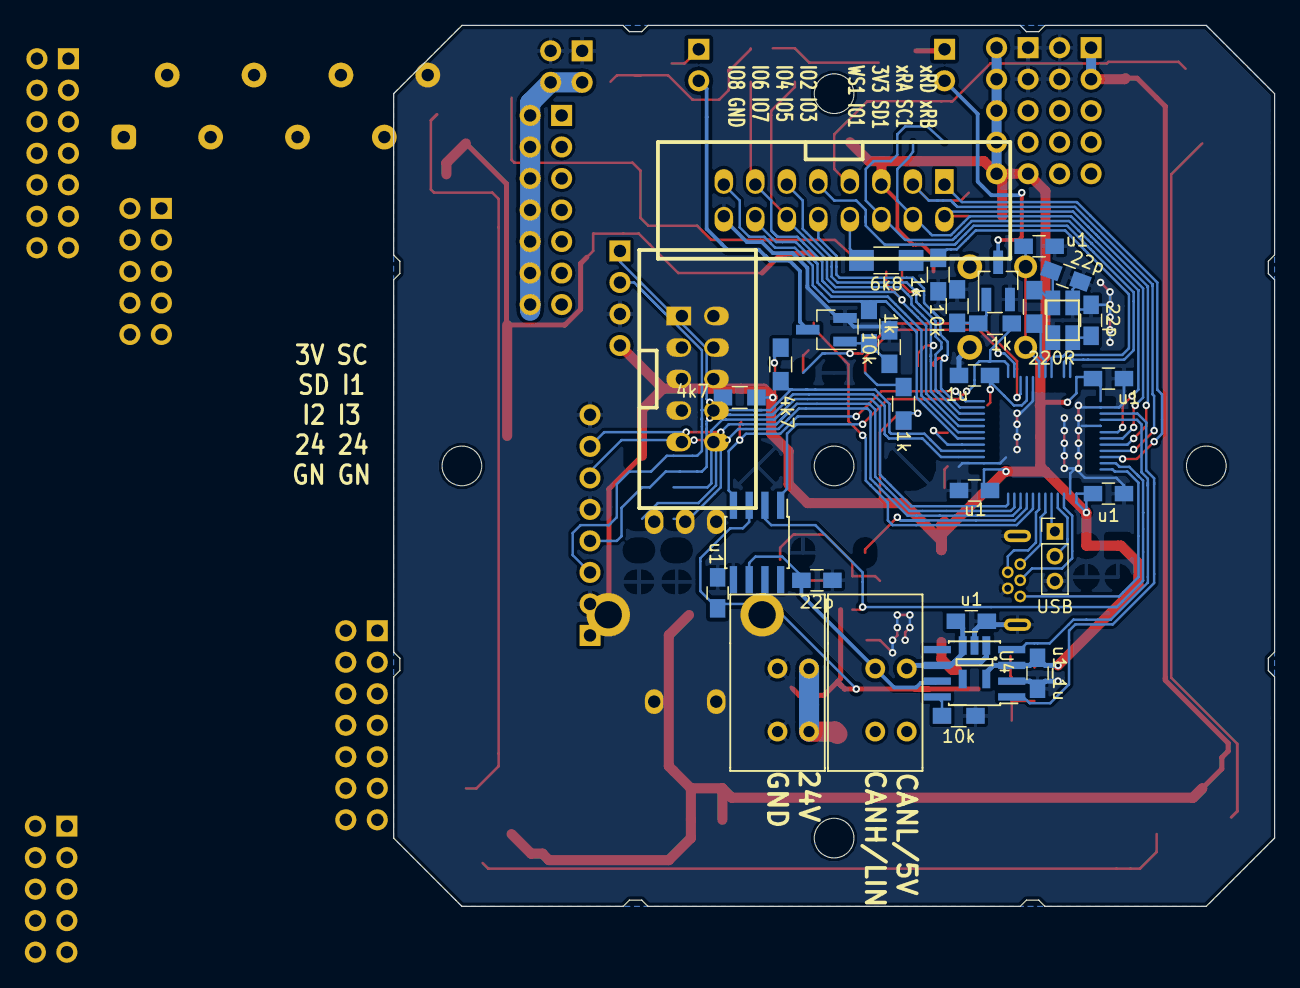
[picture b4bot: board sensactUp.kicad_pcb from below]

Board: 2 copper layers, 71.0 x 71.0 mm, 97 parts (33 on the bottom side), 50 nets.
